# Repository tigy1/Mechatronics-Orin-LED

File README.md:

# Orin Robosub LED Mode Indicator

This repository contains the firmware and host-side interface for controlling a WS2812 LED strip via an STM32 microcontroller over UART. The LEDs are used to indicate the **current operational mode** of the Orin Robosub, a student-built autonomous underwater vehicle.

Modes are communicated via UART from a Python script running on the host system and translated into LED color patterns by the STM32 firmware.

---

## Purpose

LEDs provide **immediate visual feedback** on Orin’s state. This is crucial during pool testing, debugging, or when operating the sub remotely. Modes are mapped to colors, enabling surface crew to distinguish between autonomous navigation, manual override, kill switch activation, and other states.

---

## Architecture Overview

### Hardware Components

- **Microcontroller**: STM32 (e.g., STM32F103 or similar)
- **LED Strip**: WS2812B addressable RGB strip
- **Communication**: UART @ 115200 baud between host and STM32
- **Power Supply**: Regulated 5V for LED strip

### Firmware Features (`main.c`)

- Configures **TIM2 PWM with DMA** for LED signal generation
- Parses RGB input strings over UART
- Allows **real-time LED updates** from Python terminal input
- Implements **chasing animation** based on current mode color
- Brightness control via `tan()` mapping for perceived brightness tuning

### Python Host Interface (`led_script.py`)

- Validates and sends RGB values to STM32 over UART
- Command-line interface prompts for interactive control
- Cross-platform support with adjustable serial port

---

## Getting Started

### Clone the Repository

```bash
git clone https://github.com/tigy1/Mechatronics-Orin-LED.git
cd Mechatronics-Orin-LED
```

### Build and Flash Firmware

- Use **STM32CubeIDE** or compatible toolchain
- Connect your board via ST-Link or UART bootloader
- Ensure `NUMBER_OF_LEDS` is configured correctly in `main.c`
- Flash `main.c` and its dependencies (`led.c`, `led.h`) to your board

### Install Python Dependencies

No external libraries beyond `pyserial` are required:

```bash
pip install pyserial
```

---

##  Using the Control Script

Run the Python control interface:

```bash
python3 led_script.py
```

You will be prompted to enter RGB values in the format:

```
### ### ### where each chain of hashtags represents a number 001 - 255 (0s are important) as a decimal representation of RGB values.

To disable LED output via DMA, send: `001 000 000`
```

The script will validate input and send it via UART to the STM32 board.

*Adjust `port` and `baudrate` if needed inside `led_script.py`.*

---

## Code Highlights

### UART Packet Format

The STM32 expects newline-terminated ASCII RGB strings over UART:

```
"255 000 000\n"
```

Parsed using `sscanf` in `HAL_UART_RxCpltCallback()`.

### LED Color and Brightness Encoding

Color bits are stored as bitwise-shifted PWM values in structs:

```c
typedef struct {
  uint16_t r[8], g[8], b[8];
} led;
```

Brightness mapping uses `tan(angle)` to provide nonlinear control.

### DMA Timing

Each LED gets 24 bits; additional 2 LEDs are padded to ensure reset timing:

```c
NUMBER_OF_LEDS * 24 + 2 * 24
```

---

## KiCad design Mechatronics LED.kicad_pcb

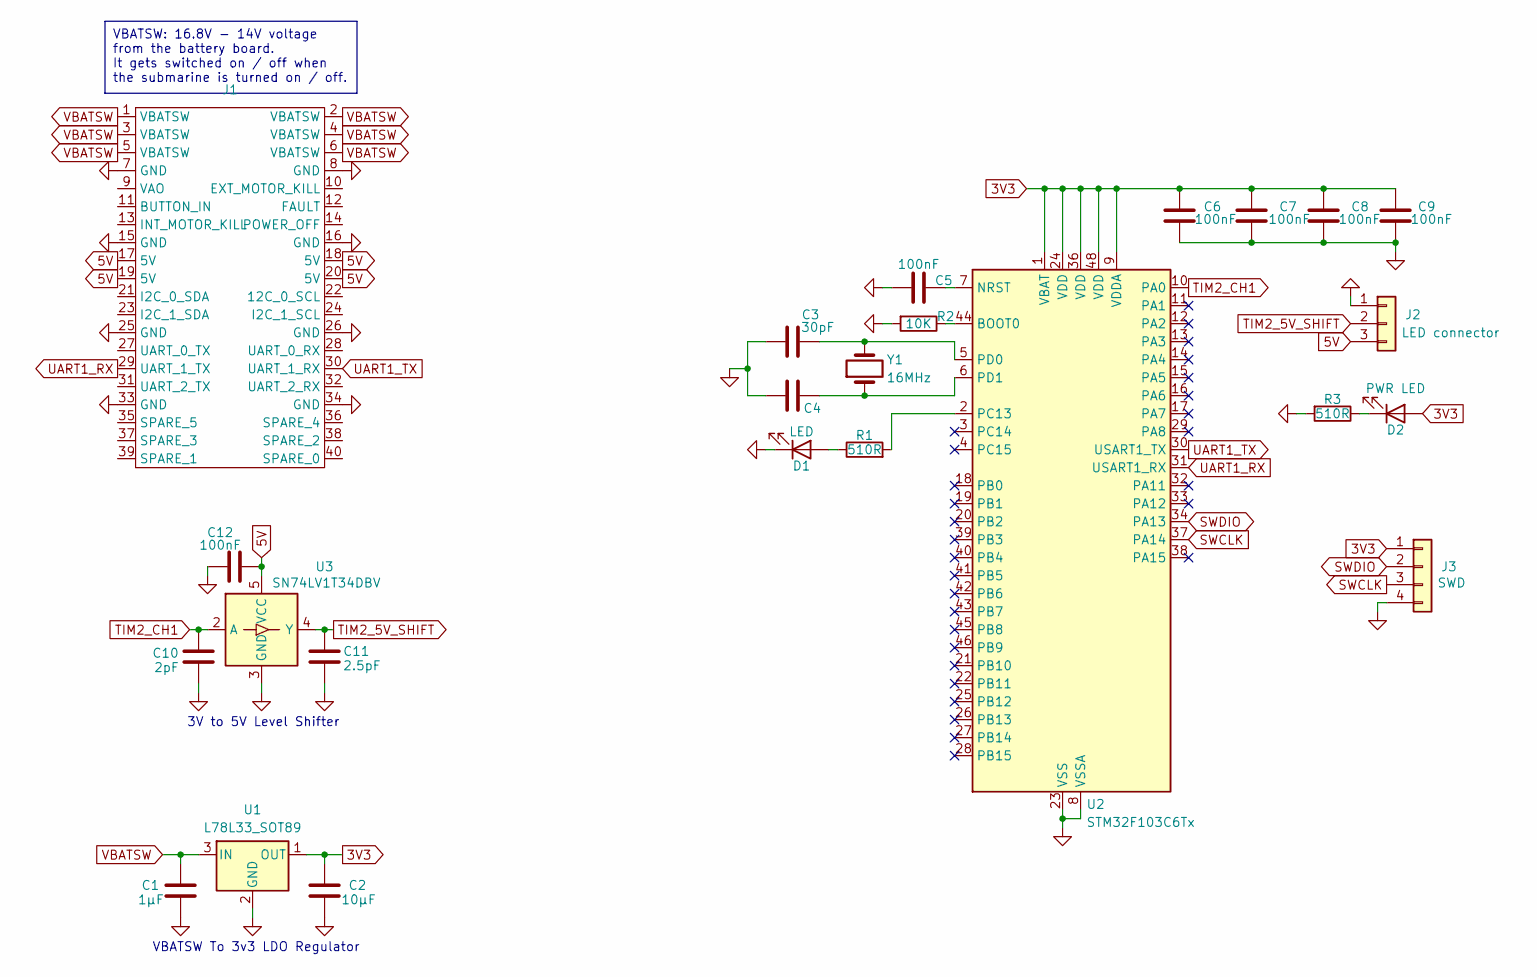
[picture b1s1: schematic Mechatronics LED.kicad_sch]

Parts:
C1: 1μF; C_0805_2012Metric
C2: 10μF; C_0805_2012Metric
C3, C4: 30pF; C_0805_2012Metric
C5, C6, C7, C8, C9, C12: 100nF; C_0603_1608Metric
C10: 2pF; C_0805_2012Metric
C11: 2.5pF; C_0805_2012Metric
D1: LED; LED_0805_2012Metric
D2: PWR LED; LED_0805_2012Metric
J1: PinHeader_2x20_P2.54mm_Vertical
J2: LED connector; PinHeader_1x03_P2.54mm_Vertical
J3: SWD; PinSocket_1x04_P2.54mm_Vertical
R1, R3: 510R; R_0805_2012Metric
R2: 10K; R_0805_2012Metric
U1: L78L33_SOT89; SOT-89-3
U2: STM32F103C6Tx; LQFP-48_7x7mm_P0.5mm
U3: SN74LV1T34DBV; SOT-23-5
Y1: 16MHz; Crystal_HC49-4H_Vertical

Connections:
3V3: C2.1, C6.1, C7.1, C8.1, C9.1, D2.2 (A), J3.1, U1.1 (OUT), U2.1 (VBAT), U2.9 (VDDA), U2.24 (VDD), U2.36 (VDD), U2.48 (VDD)
5V: C12.2, J1.17 (5V), J1.18 (5V), J1.19 (5V), J1.20 (5V), J2.3, U3.5 (VCC)
GND: C1.2, C2.2, C3.1, C4.1, C5.1, C6.2, C7.2, C8.2, C9.2, C10.2, C11.2, C12.1, D1.1 (K), J1.7 (GND), J1.8 (GND), J1.15 (GND), J1.16 (GND), J1.25 (GND), J1.26 (GND), J1.33 (GND), J1.34 (GND), J2.1, J3.4, R2.2, R3.2, U1.2 (GND), U2.8 (VSSA), U2.23 (VSS), U2.35 (VSS), U2.47 (VSS), U3.3 (GND)
unnamed: D1.2 (A), R1.1
unnamed: D2.1 (K), R3.1
unnamed: R2.1, U2.44 (BOOT0)
unnamed: C5.2, U2.7 (NRST)
unnamed: R1.2, U2.2 (PC13)
unnamed: C3.2, U2.5 (PD0), Y1.2
unnamed: C4.2, U2.6 (PD1), Y1.1
SWCLK: J3.3, U2.37 (PA14)
SWDIO: J3.2, U2.34 (PA13)
TIM2_5V_SHIFT: C11.1, J2.2, U3.4 (Y)
TIM2_CH1: C10.1, U2.10 (PA0), U3.2 (A)
UART1_RX: J1.29 (UART_1_TX), U2.31 (USART1_RX)
UART1_TX: J1.30 (UART_1_RX), U2.30 (USART1_TX)
VBATSW: C1.1, J1.1 (VBATSW), J1.2 (VBATSW), J1.3 (VBATSW), J1.4 (VBATSW), J1.5 (VBATSW), J1.6 (VBATSW), U1.3 (IN)

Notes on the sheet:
VBATSW: 16.8V - 14V voltage from the battery board. It gets switched on / off when the submarine is turned on / off.
3V to 5V Level Shifter
VBATSW To 3v3 LDO Regulator

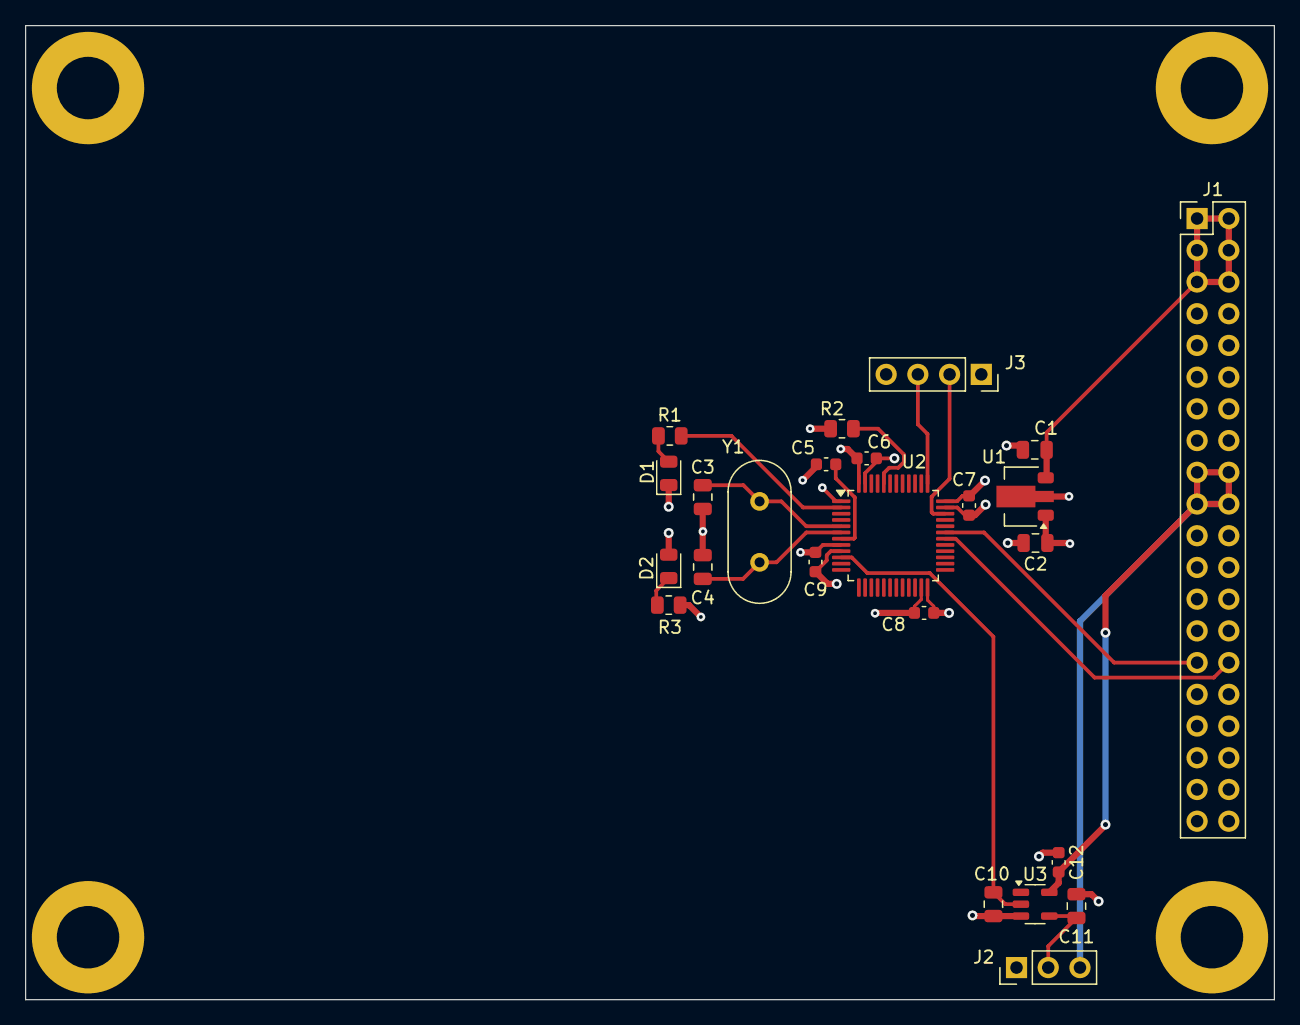
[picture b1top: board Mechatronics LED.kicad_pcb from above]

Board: 4 copper layers, 100.0 x 78.0 mm, 24 parts (0 on the bottom side), 17 nets.

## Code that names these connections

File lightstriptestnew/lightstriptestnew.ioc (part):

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Mcu.Name=STM32F103C(4-6)Tx
Mcu.Package=LQFP48
Mcu.UserName=STM32F103C6Tx
PA0-WKUP.Signal=S_TIM2_CH1_ETR
PA10.Mode=Asynchronous
PA10.Signal=USART1_RX
PA13.Mode=Serial_Wire
PA13.Signal=SYS_JTMS-SWDIO
PA14.Mode=Serial_Wire
PA14.Signal=SYS_JTCK-SWCLK
PA9.Mode=Asynchronous
PA9.Signal=USART1_TX
PC13-TAMPER-RTC.Signal=GPIO_Output
PD0-OSC_IN.Mode=HSE-External-Oscillator
PD0-OSC_IN.Signal=RCC_OSC_IN
PD1-OSC_OUT.Mode=HSE-External-Oscillator
PD1-OSC_OUT.Signal=RCC_OSC_OUT
RCC.HSEDivPLL=RCC_HSE_PREDIV_DIV2
RCC.HSE_VALUE=16000000
RCC.SYSCLKFreq_VALUE=72000000
RCC.SYSCLKSource=RCC_SYSCLKSOURCE_PLLCLK
board=custom

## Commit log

2025-05-28 Added all code for PWM LED control capabilities w/ UART
    - Inteded to run w/ UART python script to send UART data from terminal
    - Includes header & source files that store information about storing
    LED data & LED manipulation functions
    - Still incomplete, need to edit main file to clean out junk code, add
    preset LED values, and more functions to organize code
2025-05-28 Added all KiCad files for PCBLED control board
2025-06-10 Working draft of code that works w/ sending UART & PWM data
2025-06-10 Cleaned up & finalized code for LED strip setup for CaraCara sub
2025-06-10 Added LED python script for sending UART data
2025-06-21 Add list of bugs file lol
